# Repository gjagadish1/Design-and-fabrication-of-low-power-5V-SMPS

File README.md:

# Design-and-fabrication-of-low-power-5V-SMPS
Design and fabrication of a low-power 5V SMPS using KiCad involves schematic design, PCB layout, and testing. The SMPS provides efficient, regulated 5V output for low-power electronic applications.
This project focuses on the design and fabrication of a low-power 5 V Switched Mode Power Supply (SMPS) intended for efficient and compact DC power applications. The SMPS was designed using KiCad software, where the complete schematic capture and PCB layout were developed. The design typically includes an input rectification stage, high-frequency switching element, transformer or inductor, fast recovery/output rectifier, LC filtering, and a feedback control circuit to regulate the output voltage at 5 V. Emphasis was placed on component selection to minimize power loss, improve efficiency, and ensure stable operation under varying load conditions.

Using KiCad, the schematic was converted into a two-layer PCB layout with proper grounding, short high-current paths, and adequate isolation between high-voltage and low-voltage sections. After verification through ERC and DRC checks, the PCB was fabricated and assembled. The fabricated SMPS was tested for output voltage regulation, ripple, and efficiency, demonstrating reliable 5 V output suitable for low-power electronics such as microcontrollers, sensors, and embedded systems.

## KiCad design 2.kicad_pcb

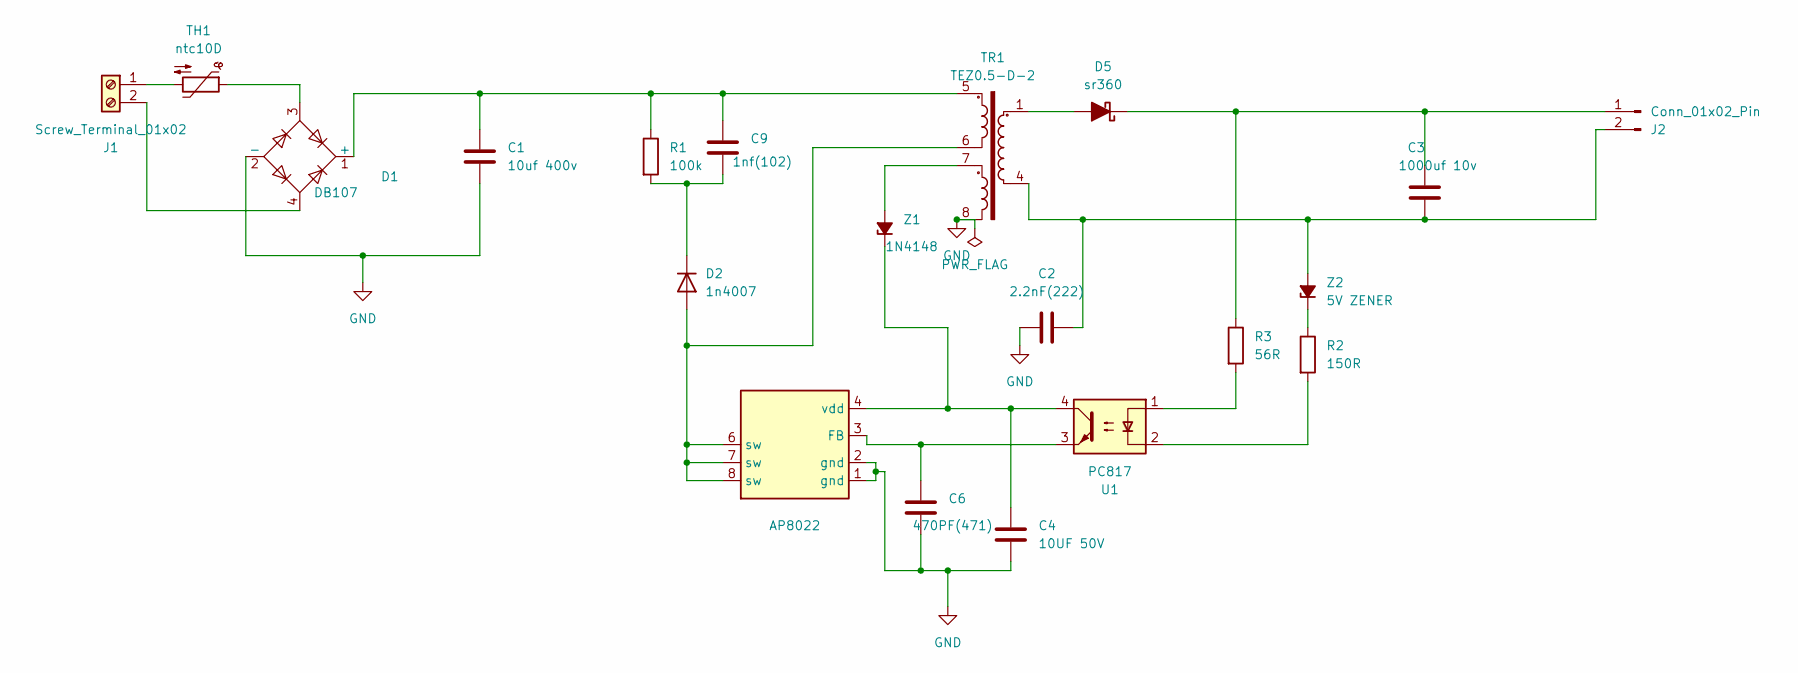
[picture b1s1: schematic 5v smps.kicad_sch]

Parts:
AP8022: ap8200
C1: 10uf 400v; C_Radial_D6.3mm_H11.0mm_P2.50mm
C2: 2.2nF(222); C_Radial_D6.3mm_H11.0mm_P2.50mm
C3: 1000uf 10v; C_Radial_D6.3mm_H11.0mm_P2.50mm
C4: 10UF 50V; C_Radial_D6.3mm_H11.0mm_P2.50mm
C6: 470PF(471); C_Radial_D6.3mm_H11.0mm_P2.50mm
C9: 1nf(102); C_Radial_D6.3mm_H11.0mm_P2.50mm
D1: DB107; Diode_Bridge_DIP-4_W7.62mm_P5.08mm
D2: 1n4007; R_Axial_DIN0204_L3.6mm_D1.6mm_P7.62mm_Horizontal
D5: sr360; D_5KPW_P7.62mm_Vertical_KathodeUp
J1: Screw_Terminal_01x02; TerminalBlock_Altech_AK300-2_P5.00mm
J2: Conn_01x02_Pin; PinHeader_1x02_P1.00mm_Horizontal
R1: 100k; R_Axial_DIN0204_L3.6mm_D1.6mm_P7.62mm_Horizontal
R2: 150R; R_Axial_DIN0204_L3.6mm_D1.6mm_P7.62mm_Horizontal
R3: 56R; R_Axial_DIN0204_L3.6mm_D1.6mm_P7.62mm_Horizontal
TH1: ntc10D; R_Axial_DIN0204_L3.6mm_D1.6mm_P2.54mm_Vertical
TR1: TEZ0.5-D-2; Transformer_Breve_TEZ-22x24
U1: PC817; DIP-4_W7.62mm
Z1: 1N4148; R_Axial_DIN0204_L3.6mm_D1.6mm_P7.62mm_Horizontal
Z2: 5V ZENER; R_Axial_DIN0204_L3.6mm_D1.6mm_P7.62mm_Horizontal

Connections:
GND: AP8022.1 (gnd), AP8022.2 (gnd), C1.2, C2.1, C4.2, C6.2, D1.2 (-), TR1.8
unnamed: AP8022.3 (FB), C6.1, U1.3
unnamed: AP8022.4 (vdd), C4.1, U1.4, Z1.1 (K)
unnamed: C1.1, C9.1, D1.1 (+), R1.1, TR1.5
unnamed: D1.3, TH1.1
unnamed: AP8022.6 (sw), AP8022.7 (sw), AP8022.8 (sw), D2.2 (A), TR1.6
unnamed: C9.2, D2.1 (K), R1.2
unnamed: D5.2 (A), TR1.1
unnamed: C3.1, D5.1 (K), J2.1, R3.1
unnamed: J1.1, TH1.2
unnamed: D1.4, J1.2
unnamed: C2.2, C3.2, J2.2, TR1.4, Z2.2 (A)
unnamed: R2.2, U1.2
unnamed: R3.2, U1.1
unnamed: TR1.7, Z1.2 (A)
unnamed: R2.1, Z2.1 (K)

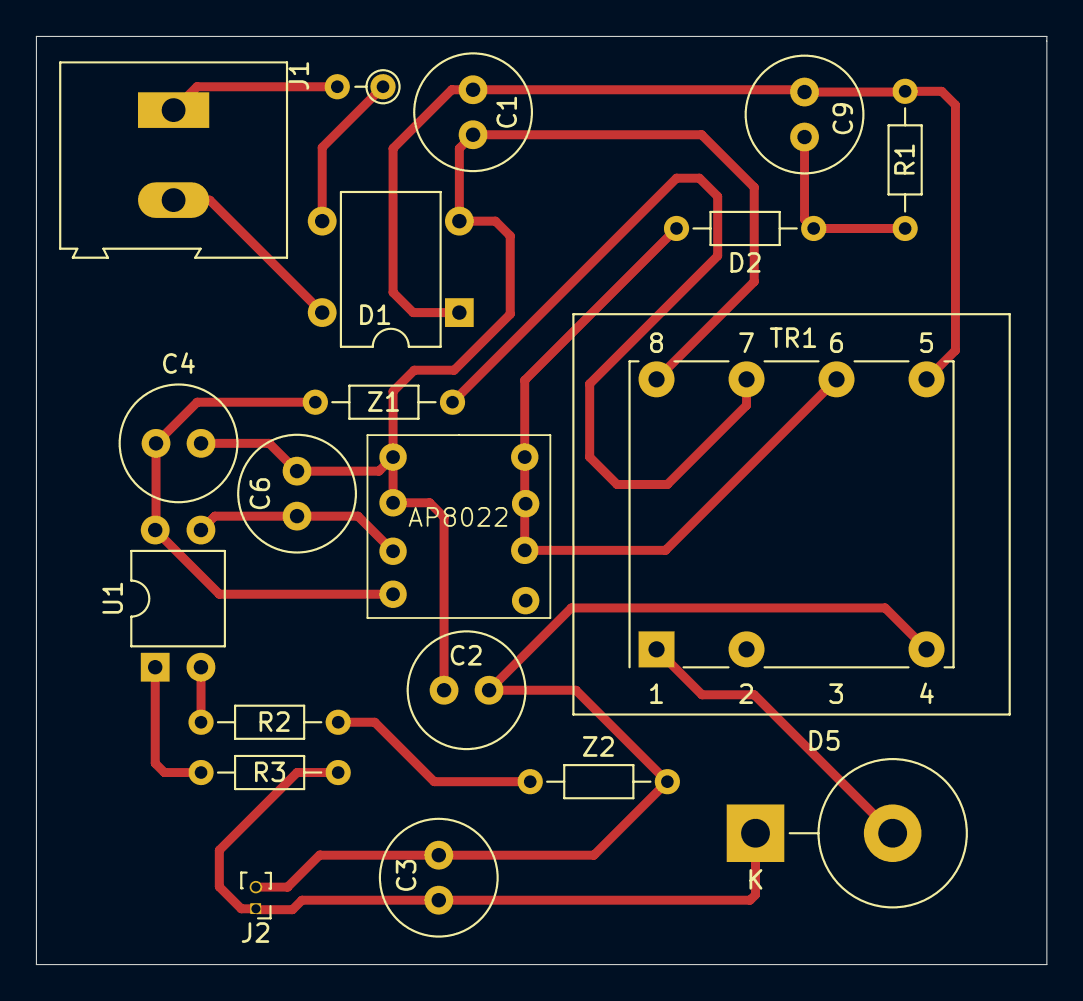
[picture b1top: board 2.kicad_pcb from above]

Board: 2 copper layers, 56.1 x 51.6 mm, 20 parts (0 on the bottom side), 16 nets.
